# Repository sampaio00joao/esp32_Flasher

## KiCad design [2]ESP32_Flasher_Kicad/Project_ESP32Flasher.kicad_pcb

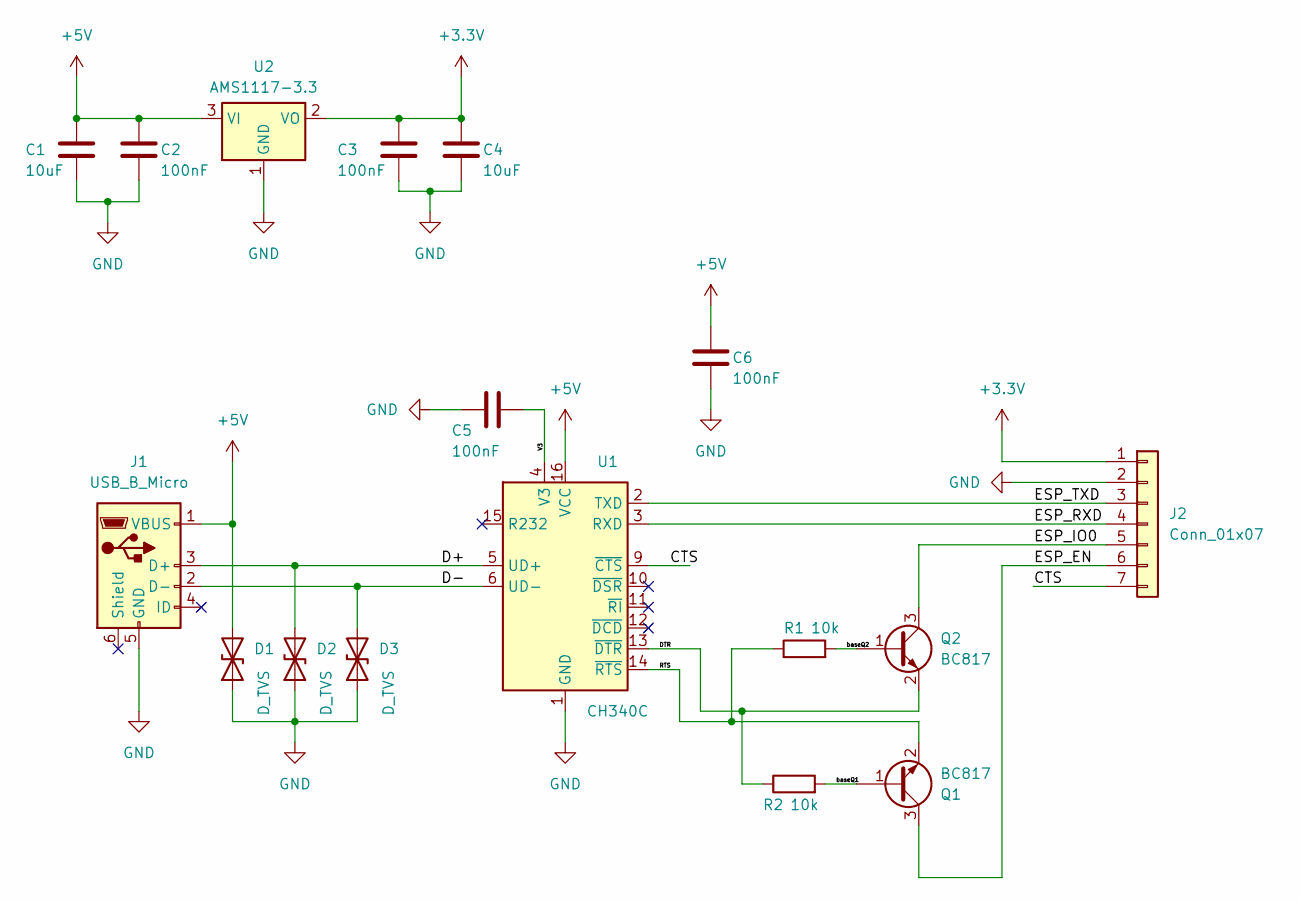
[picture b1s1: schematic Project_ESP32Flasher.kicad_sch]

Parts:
C1, C4: 10uF; C_0603_1608Metric_Pad1.08x0.95mm_HandSolder
C2, C3, C5, C6: 100nF; C_0603_1608Metric_Pad1.08x0.95mm_HandSolder
D1, D2, D3: D_TVS; D_0603_1608Metric_Pad1.05x0.95mm_HandSolder
J1: USB_B_Micro; USB_Micro-B_Molex-105017-0001
J2: Conn_01x07; PinSocket_1x07_P2.54mm_Vertical
Q1, Q2: BC817; SOT-23
R1, R2: 10k; R_0603_1608Metric_Pad0.98x0.95mm_HandSolder
U1: CH340C; SOIC-16_3.9x9.9mm_P1.27mm
U2: AMS1117-3.3; SOT-223-3_TabPin2

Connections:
+3.3V: C3.1, C4.1, J2.1, U2.2 (VO)
+5V: C1.1, C2.1, C6.1, D1.2 (A2), J1.1 (VBUS), U1.16 (VCC), U2.3 (VI)
/CTS: J2.7, U1.9 (~CTS)
/D+: D2.2 (A2), J1.3 (D+), U1.5 (UD+)
/D-: D3.2 (A2), J1.2 (D-), U1.6 (UD-)
/DTR: Q2.2 (E), R2.1, U1.13 (~DTR)
/ESP_EN: J2.6, Q1.3 (C)
/ESP_IO0: J2.5, Q2.3 (C)
/ESP_RXD: J2.4, U1.3 (RXD)
/ESP_TXD: J2.3, U1.2 (TXD)
/RTS: Q1.2 (E), R1.1, U1.14 (~RTS)
/V3: C5.1, U1.4 (V3)
/baseQ1: Q1.1 (B), R2.2
/baseQ2: Q2.1 (B), R1.2
GND: C1.2, C2.2, C3.2, C4.2, C5.2, C6.2, D1.1 (A1), D2.1 (A1), D3.1 (A1), J1.5 (GND), J2.2, U1.1 (GND), U2.1 (GND)

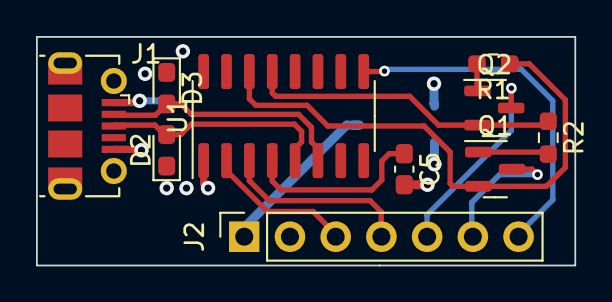
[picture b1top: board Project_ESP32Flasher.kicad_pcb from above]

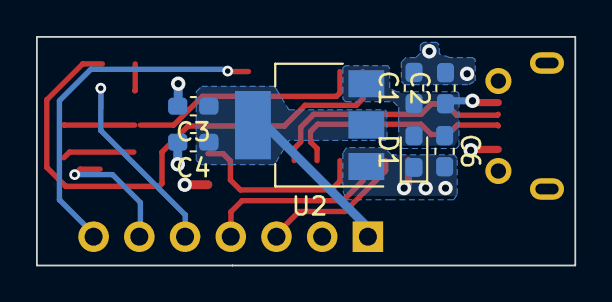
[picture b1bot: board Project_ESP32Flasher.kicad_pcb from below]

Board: 2 copper layers, 29.9 x 12.7 mm, 17 parts (7 on the bottom side), 15 nets.

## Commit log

2024-04-28 update_28/04/24
    fix "nothing inside folder"
